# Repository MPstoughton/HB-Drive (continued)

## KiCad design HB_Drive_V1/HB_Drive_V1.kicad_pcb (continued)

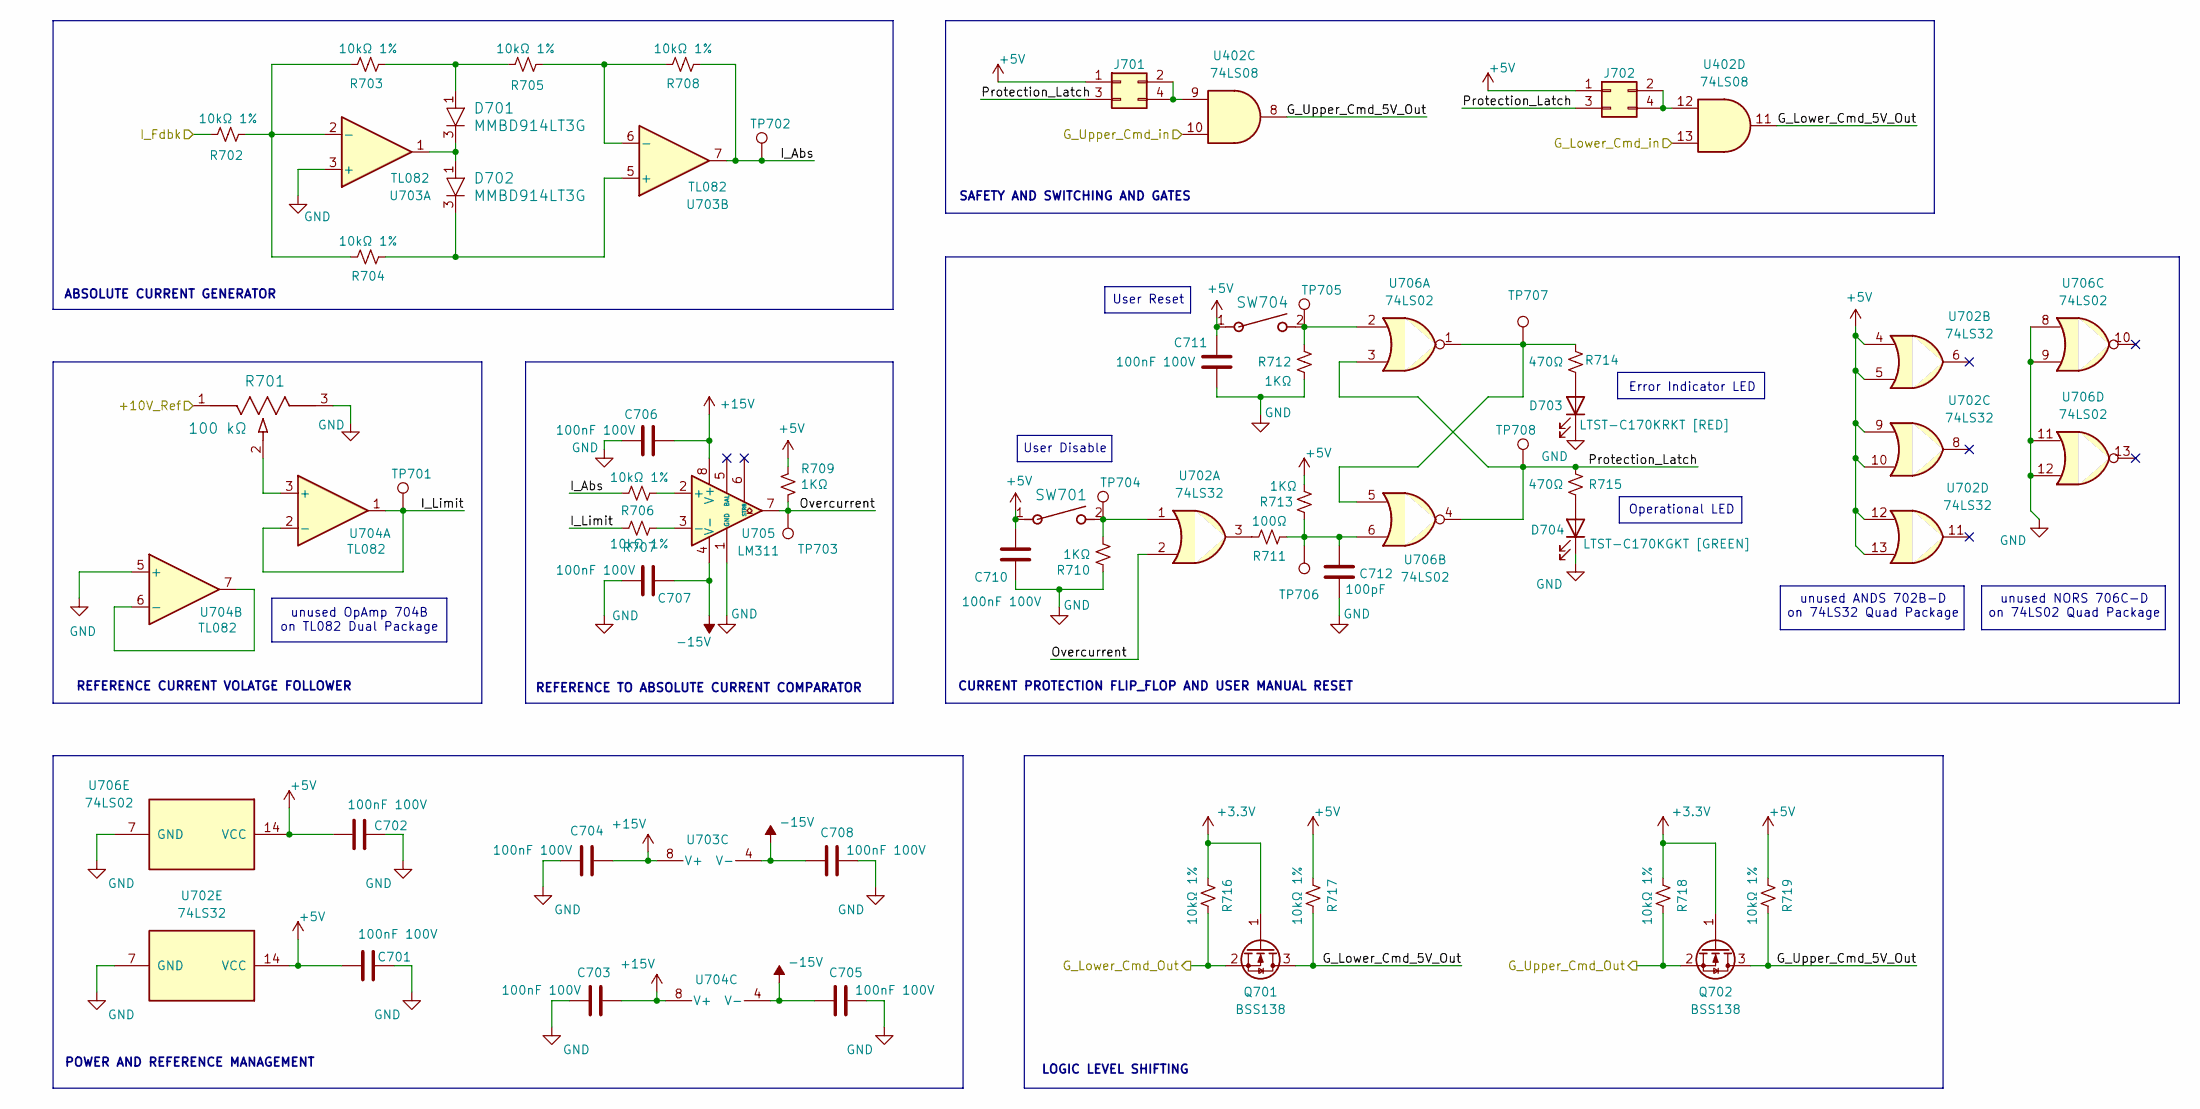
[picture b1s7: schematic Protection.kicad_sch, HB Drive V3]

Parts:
C701, C702, C703, C704, C705, C706, C707, C708, C710, C711: 100nF 100V; C_0603_1608Metric
C712: 100pF; C_0603_1608Metric
D701, D702: MMBD914LT3G; SOT-23_ONS
D703: LTST-C170KRKT [RED]; LED_0805_2012Metric_Pad1.15x1.40mm_HandSolder
D704: LTST-C170KGKT [GREEN]; LED_0805_2012Metric_Pad1.15x1.40mm_HandSolder
J701, J702: Conn_02x02_Odd_Even; PinHeader_2x02_P2.54mm_Vertical
Q701, Q702: BSS138; SOT-23
R701: 100 kΩ; POT_PV36W_BRN
R702, R703, R704, R705, R706, R707, R708, R716, R717, R718, R719: 10kΩ 1%; R_0603_1608Metric_Pad0.98x0.95mm_HandSolder
R709, R710, R712, R713: 1KΩ; R_0603_1608Metric_Pad0.98x0.95mm_HandSolder
R711: 100Ω; R_0603_1608Metric_Pad0.98x0.95mm_HandSolder
R714, R715: 470Ω; R_0603_1608Metric_Pad0.98x0.95mm_HandSolder
SW701, SW704: PTS636SL43SMTRLFS
TP701, TP702, TP703, TP704, TP705, TP706, TP707, TP708: TestPoint; TestPoint_Loop_D2.60mm_Drill1.6mm_Beaded
U402: 74LS08; SOIC-14_3.9x8.7mm_P1.27mm
U702: 74LS32; SOIC-14_3.9x8.7mm_P1.27mm
U703, U704: TL082; SOIC-8_3.9x4.9mm_P1.27mm
U705: LM311; SOIC-8_3.9x4.9mm_P1.27mm
U706: 74LS02; SOIC-14_3.9x8.7mm_P1.27mm

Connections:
+3.3V: Q701.1 (G), Q702.1 (G), R716.2, R718.2; also elsewhere on the board
+5V: C701.2, C702.2, C710.1, C711.1, J701.1, J702.1, R709.2, R713.2, R717.2, R719.2, SW701.1, SW704.1, U702.4, U702.5, U702.9, U702.10, U702.12, U702.13, U702.14 (VCC), U706.14 (VCC); also elsewhere on the board
+15V: C703.1, C704.1, C706.1, U703.8 (V+), U704.8 (V+), U705.8 (V+); also elsewhere on the board
-15V: C705.2, C707.1, C708.2, U703.4 (V-), U704.4 (V-), U705.4 (V-); also elsewhere on the board
/+10V_Ref: R701.1; also elsewhere on the board
/G_Lower_Cmd: Q701.2 (S), R716.1; also elsewhere on the board
/G_Upper_Cmd: Q702.2 (S), R718.1; also elsewhere on the board
/Inner Current Regulator/-I_Fdbk: R702.1; also elsewhere on the board
/Modulator and Protection/Modulator and Dead Time Injector/G_Lower_Cmd: U402.13; also elsewhere on the board
/Modulator and Protection/Modulator and Dead Time Injector/G_Upper_Cmd: U402.10; also elsewhere on the board
/Modulator and Protection/Protection/G_Lower_Cmd_5V_Out: Q701.3 (D), R717.1, U402.11
/Modulator and Protection/Protection/G_Upper_Cmd_5V_Out: Q702.3 (D), R719.1, U402.8
/Modulator and Protection/Protection/I_Abs: R706.1, R708.2, TP702.1 (1_1), U703.7
/Modulator and Protection/Protection/I_Limit: R707.2, TP701.1 (1_1), U704.1, U704.2 (-)
/Modulator and Protection/Protection/Overcurrent: R709.1, TP703.1 (1_1), U702.2, U705.7
/Modulator and Protection/Protection/Protection_Latch: J701.3, J702.3, R715.2, TP708.1 (1_1), U706.3, U706.4
GND: C701.1, C702.1, C703.2, C704.2, C705.1, C706.2, C707.2, C708.1, C710.2, C711.2, C712.1, D703.1 (K), D704.1 (K), R701.3, R710.1, R712.1, U702.7 (GND), U703.3 (+), U704.5 (+), U705.1 (GND), U706.7 (GND), U706.8, U706.9, U706.11, U706.12; also elsewhere on the board
unnamed: C712.2, R711.2, R713.1, TP706.1 (1_1), U706.6
unnamed: D701.1, R703.2, R705.1
unnamed: D701.3, D702.1, U703.1
unnamed: D703.2 (A), R714.1
unnamed: D704.2 (A), R715.1
unnamed: J701.2, J701.4, U402.9
unnamed: J702.2, J702.4, U402.12
unnamed: R710.2, SW701.2, TP704.1 (1_1), U702.1
unnamed: R711.1, U702.3
unnamed: R712.2, SW704.2, TP705.1 (1_1), U706.2
unnamed: R714.2, TP707.1 (1_1), U706.1, U706.5
unnamed: R702.2, R703.1, R704.1, U703.2 (-)
unnamed: D702.3, R704.2, U703.5 (+)
unnamed: R705.2, R708.1, U703.6 (-)
unnamed: R701.2, U704.3 (+)
unnamed: U704.6 (-), U704.7
unnamed: R706.2, U705.2 (+)
unnamed: R707.1, U705.3 (-)

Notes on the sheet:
Operational LED
CURRENT PROTECTION FLIP_FLOP AND USER MANUAL RESET
SAFETY AND SWITCHING AND GATES
User Reset
ABSOLUTE CURRENT GENERATOR
POWER AND REFERENCE MANAGEMENT
LOGIC LEVEL SHIFTING
Error Indicator LED
unused NORS 706C-D on 74LS02 Quad Package
REFERENCE CURRENT VOLATGE FOLLOWER
REFERENCE TO ABSOLUTE CURRENT COMPARATOR
User Disable
unused ANDS 702B-D on 74LS32 Quad Package
unused OpAmp 704B on TL082 Dual Package

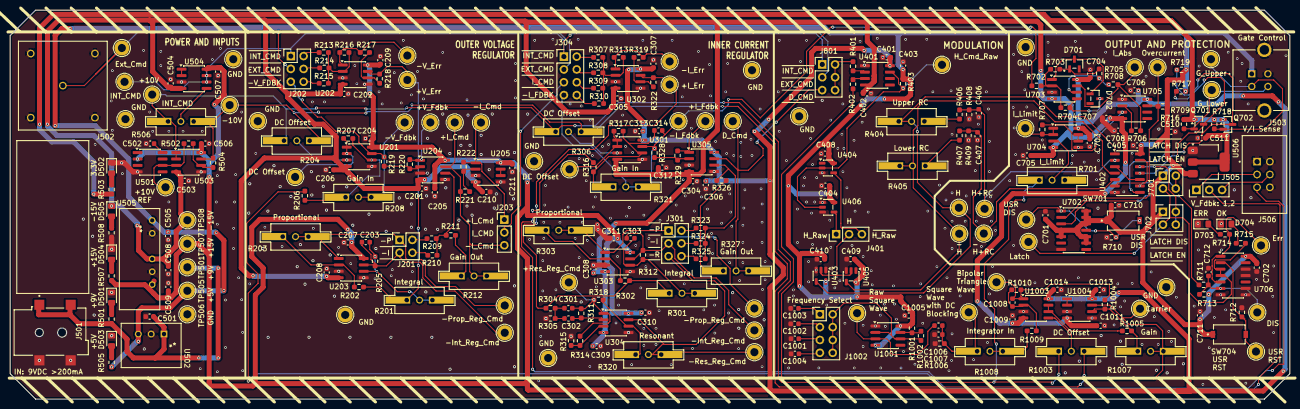
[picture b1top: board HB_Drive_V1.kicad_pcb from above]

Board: 2 copper layers, 253.2 x 77.0 mm, 282 parts (0 on the bottom side), 137 nets.

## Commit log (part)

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2026-06-11 Initial KiCad project setup
2026-06-11 Adds Preliminary Hierarchical Schematics
2026-06-12 fixes git and adds a first revision of the Inner Current Regulator (NOT COMPLETE)
2026-06-12 Finishes first revision of the Inner Current Regulator!
2026-06-15 Adds Carrier Wave Circuit and Comparator Circuit
2026-06-16 Notes from conversation PF + MS
2026-06-23 adds 10v reference and DC offsets / gain control to I_fdbk and V_fdbk
